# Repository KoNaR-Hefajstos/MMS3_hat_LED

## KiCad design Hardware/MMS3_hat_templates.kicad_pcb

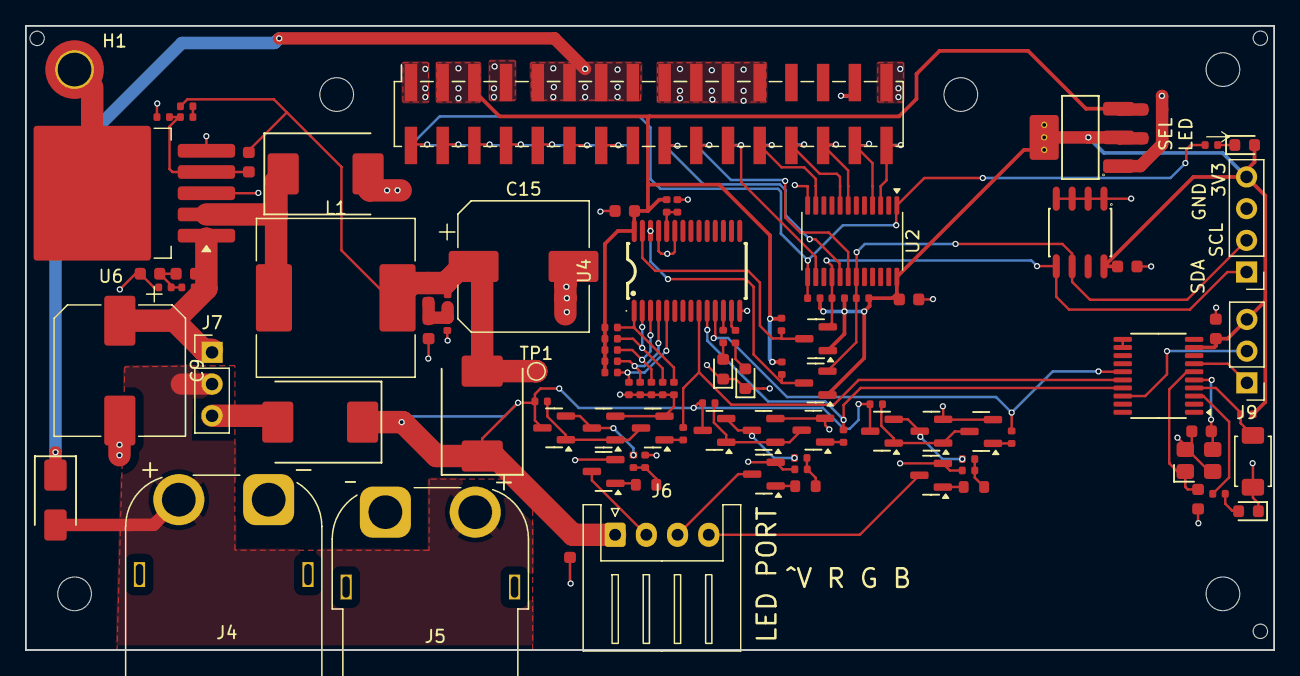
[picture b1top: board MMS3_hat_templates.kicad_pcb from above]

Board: 4 copper layers, 100.0 x 50.0 mm, 109 parts (1 on the bottom side), 74 nets.

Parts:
C1, C2: 10uF; C_0603
C3, C4, C5, C6, C10, C11, C13, C14, C16: 100nF; C_0603
C9, C15: 100uF; CP_Elec_10x10
C12: 3.3nF; C_0603
C17, C18: 12pF; C_0603
D1, D3, D4, D9: Red; D_0603
D2: M7; D_SMA
D6, D8, D10: SS510C; D_SMC
H1: M2.5 Mount; MountingHole_2.7mm_M2.5_DIN965_Pad_TopOnly
H2, H3, H4, H5, H6: M2.5 mount; MountingHole_2.7mm_M2.5
H7, H8, H9: Hole_Tooling_JLCPCB
J1: Chainbus in; PinHeader_2x16_P2.54mm_Vertical_SMD
J2: Chainbus Out; PinSocket_2x16_P2.54mm_Vertical_SMD
J3: Conn_01x04_Pin; PinHeader_1x04_P2.54mm_Vertical
J4: AMASS XT60 Male; AMASS_XT60PW-M_1x02_P7.20mm_Horizontal
J5: AMASS XT60 Female; AMASS_XT60PW-F_1x02_P7.20mm_Horizontal
J6: LED connector; JST_XH_S4B-XH-A_1x04_P2.50mm_Horizontal
J7: Conn_01x03_Pin; PinHeader_1x03_P2.54mm_Vertical
J9: Program; PinHeader_1x03_P2.54mm_Vertical
L1: 100uH 4A; L_Sunlord_SWRB1207S
Q1, Q13, Q27: AO3400A; Q_SOT-23
Q2, Q3, Q7, Q8, Q10, Q11: MMBT2222A 1P; Q_SOT-23
Q4, Q9, Q12: MMBT5401 200-300; Q_SOT-23
Q25, Q26: 2N7002K; Q_SOT-23
R4, R8, R10, R14, R15, R16, R17, R18, R19, R20, R21, R22, R23, R24, R25, R26, R32, R51, R62, R71, R72: 10kΩ; R_0402
R11, R30, R38, R42, R52: 330Ω; R_0402
R12, R13: 510Ω; R_0402
R27, R36, R40: 1kΩ; R_0402
R28, R31, R61: 100Ω; R_0603
R33, R39, R43: 47Ω; R_0402
R44, R45, R47, R49, R50: 33kΩ; R_0402
R46: 3.9kΩ; R_0402
R48: 1.2kΩ; R_0402
S1: Tactile Button, 160gf; SW_TS-1088-AR02016
TP1: TestPoint; TestPoint_Pad_D1.0mm
U1: AMS1117; SOT-223-3_L6.5-W3.4-P2.30-LS7.0-BR
U2: SN74CB3Q3384APW; TSSOP-24_4.4x7.8mm_P0.65mm
U3: M24C64; SOIC-8_L5.0-W4.0-P1.27-LS6.0-BL
U4: PCA9685PW,118; TSSOP-28_L9.7-W4.4-P0.65-LS6.4-TL
U6: LM2596HVS-ADJRG; TO-263-5_TabPin3
U7: CH32V003FxPx; TSSOP-20_4.4x6.5mm_P0.65mm
X1: X322525MOB4SI; OSC-SMD_4P-L3.2-W2.5-BL

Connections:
+3V3: C2.1, C3.1, C4.1, C16.1, D1.2, J3.4, J9.3, Q25.1 (G), Q26.1 (G), R4.1, R8.1, R10.2, R51.1, U1.2 (VOUT), U1.4 (VOUT), U2.24 (VCC), U3.8 (VCC), U7.9 (VDD)
+5V: C1.1, C5.1, J1.3, J1.5, J2.3, J2.5, R14.1, R16.1, R18.1, R20.1, R22.1, R24.1, R71.1, R72.1, U1.3 (VIN), U4.28 (VDD)
+12V stby: J1.29, J2.29
/12V: C6.1, D8.1, D10.1, J6.1, Q3.3 (C), Q8.3 (C), Q11.3 (C), R30.1, R38.1, R42.1
/B2: R40.1, U4.11 (LED5), U7.15 (PC5)
/Buck Regulator/VIN_BRD: D2.2, J4.2, J5.2, J7.2
/Buck Regulator/sw: D6.1, L1.1, U6.2 (OUT)
/Buck Regulator/sw-vin: C9.1, C10.1, J7.1, R44.1, U6.1 (VIN)
/Bus_switch/Chainbus.SCL: J3.2, Q25.2 (S), R4.2, U2.19 (2B3), U3.6 (SCL)
/Bus_switch/Chainbus.SDA: J3.1, Q26.2 (S), R8.2, U2.16 (2B2), U3.5 (SDA)
/Bus_switch/Chainbus_In.CS: J1.22, J2.22, U2.14 (2A1)
/Bus_switch/Chainbus_In.MISO: J1.28, J2.28, U2.7 (1A3)
/Bus_switch/Chainbus_In.MOSI: J1.26, J2.26, U2.8 (1A4)
/Bus_switch/Chainbus_In.RX: J1.32, J2.32, U2.3 (1A1)
/Bus_switch/Chainbus_In.SCK: J1.24, J2.24, U2.11 (1A5)
/Bus_switch/Chainbus_In.SCL: J1.20, J2.20, U2.18 (2A3)
/Bus_switch/Chainbus_In.SDA: J1.18, J2.18, U2.17 (2A2)
/Bus_switch/Chainbus_In.TX: J1.30, J2.30, U2.4 (1A2)
/Bus_switch/SEL1: J1.2, R10.1, R11.1, U2.1 (~1OE), U2.13 (~2OE)
/CH32V003/CH32V003.RX: R52.1, U7.3 (PD6)
/CH32V003/OSCI: C17.1, U7.5 (PA1), X1.3 (OSC)
/CH32V003/OSCO: C18.1, U7.6 (PA2), X1.1 (OSC)
/CH32V003/PD7: R51.2, S1.1 (A), U7.4 (PD7)
/CH32V003/SWIO: J9.2, U7.18 (PD1)
/Chainbus.SDA: U7.11 (PC1), U7.12 (PC2)
/G2: R36.1, U4.10 (LED4), U7.17 (PC7)
/Interboard_connector/SEL2: J1.4, J2.2
/Interboard_connector/SEL3: J1.6, J2.4
/Interboard_connector/SEL4: J1.8, J2.6
/Interboard_connector/SEL5: J1.10, J2.8
/Interboard_connector/SEL6: J1.12, J2.10
/Interboard_connector/SEL7: J1.14, J2.12
/Interboard_connector/SEL8: J1.16, J2.14
/LEDController1/Bin: J6.4, Q27.3 (D)
/LEDController1/Gin: J6.3, Q13.3 (D)
/LEDController1/Rin: J6.2, Q1.3 (D)
/LEDController1/S1: R26.2, R28.1, R33.2
/LEDController1/S2: R31.1, R32.2, R39.2
/LEDController1/S3: R43.2, R61.1, R62.2
/LED_IC/A0: R24.2, R25.1, U4.1 (A0)
/LED_IC/A1: R22.2, R23.1, U4.2 (A1)
/LED_IC/A2: R20.2, R21.1, U4.3 (A2)
/LED_IC/A3: R18.2, R19.1, U4.4 (A3)
/LED_IC/A4: R16.2, R17.1, U4.5 (A4)
/LED_IC/A5: R14.2, R15.1, U4.24 (A5)
/LED_IC/S15: R12.1, U4.12 (LED6)
/LED_IC/S16: R13.1, U4.13 (LED7)
/LED_IC/SCL_5V: Q25.3 (D), R71.2, U4.26 (SCL)
/LED_IC/SDA_5V: Q26.3 (D), R72.2, U4.27 (SDA)
/R2: R27.1, U4.9 (LED3), U7.16 (PC6)
GND: C1.2, C2.2, C3.2, C4.2, C5.2, C6.2, C9.2, C11.2, C14.2, C15.2, C16.2, C17.2, C18.2, D3.1, D4.1, D6.2, D9.1, H1.1 (1_1), J1.1, J1.7, J1.17, J1.19, J1.21, J1.23, J1.31, J2.1, J2.7, J2.17, J2.19, J2.21, J2.23, J2.31, J3.3, J4.1, J5.1, J9.1, Q1.2 (S), Q2.2 (E), Q4.2 (E), Q7.2 (E), Q9.2 (E), Q10.2 (E), Q12.2 (E), Q13.2 (S), Q27.2 (S), R15.2, R17.2, R19.2, R21.2, R23.2, R25.2, R26.1, R32.1, R45.2, R46.1, R50.2, R62.1, S1.2 (B), U1.1 (GND), U2.12 (GND), U3.1 (A0), U3.2 (A1), U3.3 (A2), U3.4 (VSS), U4.14 (VSS), U4.23 (~OE), U4.25 (EXTCLK), U6.3 (GND), U6.5 (~ON/OFF), U7.7 (VSS), X1.2 (GND), X1.4 (GND)
unnamed: C10.2, C11.1, R44.2, R45.1
unnamed: C12.2, C13.1, C15.1, D10.2, L1.2, R48.2, R49.1, TP1.1 (1_1)
unnamed: C13.2, C14.1, R49.2, R50.1
unnamed: D1.1, R11.2
unnamed: D3.2, R12.2
unnamed: D4.2, R13.2
unnamed: D9.2, R52.2
unnamed: D8.2, J7.3
unnamed: Q1.1 (G), R28.2
unnamed: Q2.1 (B), R27.2
unnamed: Q2.3 (C), Q3.1 (B), Q4.1 (B), R30.2
unnamed: Q3.2 (E), Q4.3 (C), R33.1
unnamed: Q7.1 (B), R36.2
unnamed: Q7.3 (C), Q8.1 (B), Q9.1 (B), R38.2
unnamed: Q8.2 (E), Q9.3 (C), R39.1
unnamed: Q10.1 (B), R40.2
unnamed: Q10.3 (C), Q11.1 (B), Q12.1 (B), R42.2
unnamed: Q11.2 (E), Q12.3 (C), R43.1
unnamed: Q13.1 (G), R31.2
unnamed: Q27.1 (G), R61.2
unnamed: R47.2, R48.1
unnamed: C12.1, R46.2, R47.1, U6.4 (FB)
VIN_CHAINBUS: D2.1, J1.9, J1.11, J1.13, J1.15, J2.9, J2.11, J2.13, J2.15

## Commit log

2026-05-14 Scheme
2026-05-21 Schematic
2026-05-21 fork adjustment
2026-05-23 reviev by Wojtek
2026-05-25 schemat
2026-05-27 Schematic touchup
2026-06-03 PCB design
    Hat allows to connect 1 LED tape at a time
2026-06-09 PCB addjustments
